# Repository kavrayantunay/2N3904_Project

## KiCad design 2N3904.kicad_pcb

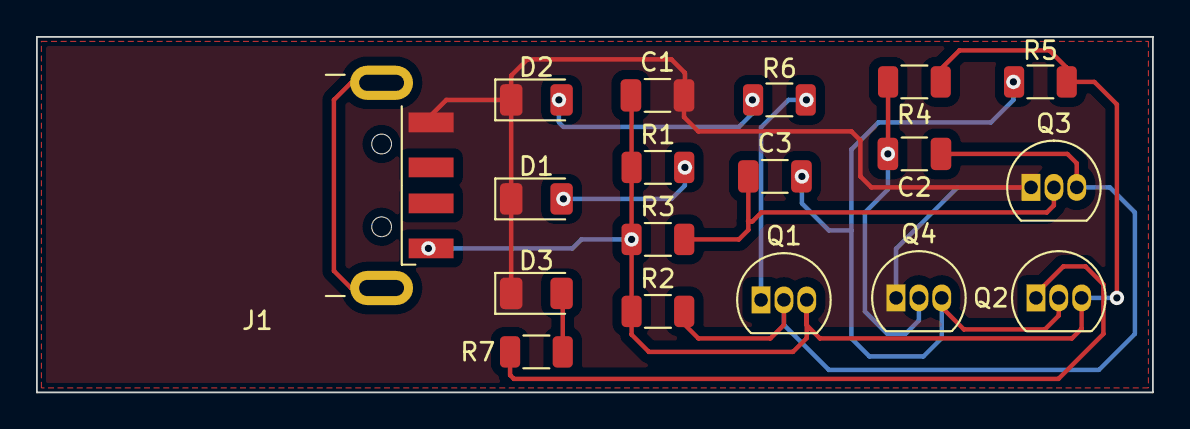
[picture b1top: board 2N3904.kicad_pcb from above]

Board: 2 copper layers, 62.0 x 19.8 mm, 18 parts (0 on the bottom side), 11 nets.

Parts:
C1, C2, C3: 10uF; C_1206_3216Metric
D1, D2, D3: LED; LED_1206_3216Metric
J1: USB_A; USB_A_CNCTech_1001-011-01101_Horizontal
Q1, Q2, Q3, Q4: 2N3904; TO-92_Inline
R1, R6, R7: 1k; R_1206_3216Metric
R2, R5: 10k; R_1206_3216Metric
R3, R4: 100k; R_1206_3216Metric

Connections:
GND: C1.2, D1.1 (K), D2.1 (K), D3.1 (K), J1.4 (GND), Q3.1 (E), Q4.1 (E)
unnamed: C1.1, J1.1 (VBUS), Q1.3 (C), Q2.3 (C), R1.1, R2.1, R3.1, R4.1, R5.1
unnamed: C2.1, Q1.2 (B), Q3.3 (C), R2.2
unnamed: C2.2, Q4.2 (B), R4.2
unnamed: C3.1, Q3.2 (B), R3.2
unnamed: C3.2, Q2.2 (B), Q4.3 (C), R5.2
unnamed: D1.2 (A), R1.2
unnamed: D2.2 (A), R6.2
unnamed: D3.2 (A), R7.2
unnamed: Q1.1 (E), R6.1
unnamed: Q2.1 (E), R7.1
